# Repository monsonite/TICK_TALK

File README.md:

# TICK_TALK
## An experimental 8-bit, bit serial computer.

## Hebden Bridge Workshop Update  25-08-24

OSHCamp 2024

TICK Workshop Update.

Thanks to the 16 people who attended the 1st TICK workshop session at Hebden Bridge, on Sunday August 25th.

Most kits were assembled without too many problems, and several were close to completion at the end of the afternoon.

Unfortunately some components were misplaced and not found until late in the afternoon, close to packing up time, but workarounds were employed.

Attendees should make contact me via email at k*n.boat@gmail.com - replacing the "t" with the 1st letter of my 1st name.

### Points Arising.

1.  The 74HC4060.dig file is now available. Download it and place it in the Lib  (libraries) folder of where you have installed "Digital"  - ideally under 

\Digital\Digital\lib\DIL Chips\74xx\counter

Then restart Digital and select components, custom, update and it should then be available.

2. Tick now has a Hackaday.io project page here:

https://hackaday.io/project/197333-tick-a-novel-homebrew-mcu-architecture-in-28-ics

Please feel free to join the project team and message me in the team messaging section.

3. It would be sensible to convert the Eagle CAD pcb schematic and pcb layout files to KiCad - to allow greater accessibility to interested users. I will investigate importing the schematic into Kicad, with the aim of generating the next iteration of the pcb using Kicad.

4. As the workshop was primarily focussed on assembly of the pcb in the time available, the Pi Pico firmware aspects of the project remained virtually unmentioned.

The principal role of the Pico is to emulate a 64K x16-bit ROM. It does this by "sniffing" the ROM address lines generated from the Program Counter, and using the two 74HC595 shift registers (U26, U27) located under the Pi Pico, to output the 16-bit value from that ROM address onto the Instruction Bus.

5. The 6-way JST cables supplied will allow the Pi Pico access to both the ROMulator Port X2 (on the left) and the SPI Port X1 (on the right). Details of these connectors and the modifications to the wiring of the cable to the Pico GPIO pins 18 to 21 and 26 to 29 will be released shortly in a separate document'

6.  I have received notification from PCBWay in China and they are prepared to sponsor the manufacture of the next version of the Tick PCB.

I am tempted to have a SMT version assembled in China - so it will be smaller, lighter and have better features.

I would like your feedback over, whether you would like to receive this SMT version in the Autumn.

Please send feedback to my Gmail address.

Ken

Update  - Lissa has created a new discord server for TICK

try this invite code.

https://discord.gg/FmW9dqFGb5

/*************************************************************************************************************************

TICK is an experimental 8-bit, serial arithmetic CPU designed around the commonly available 74HCxx logic series.

TICK uses 26 74HXxx ICs, plus a 32K byte RAM and a 64K x 16-bit ROM - or a ROM emulator.

TICK fits onto a 4-layer PCB, sized just 110mm x 110mm. It has 5 principal connectors that allow you to access all of the main signals and buses. Low cost 6-way JST XH ribbon cables are used to hook up the TICK serial interface bus and the Pi Pico SPI.  A 40 way 2.54mm pitch header allows access to the parallel buses.

USB (power) is supplied either through a USB microB connector or via USB C connector of the the Clone Pi Pico "ROMulator".

PCB Headers are included that will allow a very low-cost Raspberry Pi Pico (clone) to be plugged in, providing emulation of the ROM and also implementing a simple serial interface to a laptop or PC.

TICK has evolved slowly over several months, and this repo reflects the most recent design files, manufacturing data and BOM. The earlier repo "TICK" is purely reserved for earlier work. All current and future developments will be documented here.

TICK started life a few months ago and is highly influenced by the the developments I did on "MITE" its 16-bit Cousin. Here the basics of the timing pulse generator and ALU were thashed out to the point that I am happy to utilise them in a new design.

Much of the combinational logic has been rationalised, and short of implementing the ALU and control logic in a ROM, I believe that I have reached a point where the logic is stable, and not reduced to a blackbox ROM.

TICK is 26 74HCxx ICs plus a ROM and RAM.

The ICs are utilised in 5 main sub-circuits:

1. Clock Sequencer and Timing Pulse Generator.

2. Instruction Decoder

3. ALU and PC Incrementer, plus Jump logic.

4. Memory Control Hardware.

5. GPIO and ROMulator interfaces.

In an ideal world,  TICK would be a BlackBox with just 2 wires for power, and 2 wires for data in and data out. If you look at a landline telephone or broadband modem, they only have 2 wires or 4 wires. However for the purposes of this project we reqire syncronous data transfer - and that needs a clock that is shared between all nodes.

In general terms, TICK communicates with external devices via an SPI compatible interface.

## Architecture

TICK is highly influenced by Marcel van Kervinck's 8-bit Gigatron TTL Computer. The Gigatron used ten ICs in its ALU, I can do it serially in two. However a bit-serial design needs additional ICs to implement the clock sequencer, the timing pulse generator and the SRAM and Jump logic.

It is very marginal whether an 8-bit serial architecture will have fewer ICs than an 8-bit parallel design. Bit Serial really comes into fruition when you have a wordsize of 16 or more bits.

So the motivation for developing TICK was to make an intelligent node that can interface to SPI serial peripherals and other intelligent nodes. It won't be the fastest computer on the planet - but it should be able to compete with 1970s/80s 8-bit workhorses, like the 6502, Z80, 8051, 6309 etcand even older machines that predate the microprocessor - such as the  PDP-8 (1965) and the EDUC8 (1974).

TICK is a modified Harvard architecture.  Address and data from the ROM are conveyed on separate buses to those of the RAM. Simple shift registers are used to convert between the serial and parallel domains. A task that they can do very efficiently.

### Registers

TICK has a single 8-bit accumulator AC. AC may be loaded with an 8-bit literal direct from the lower 8 ROM data lines, or AC can be loaded with data addressed from the 32K x 8-bit SRAM.

As well as the Accumulator AC, TICK has a 16-bit wide general purpose register known as the B-Register. The B-Reg is 16-bits wide, in order to accept a 16-bit word, in parallel from the ROM and either use that as a indirect RAM address, or load it into the ROM Program Counter (PC) to perform a Conditional Branch or a 16-bit Long Jump.

The PC mentioned above is also 16-bits wide and can cover the full 16 bits of the ROM addressing range. A 16-bit jump is non-conditional, but an 8-bit "page" branch is conditional on the ZERO and SIGN flags from the Accumulator.

## Circuit Description (Draft 20-08-24)

Tick is an experimental, 8-bit, bit serial computer designed to interface to SPI peripherals and memory.

It has a 16-bit Program Counter, a 16-bit B-Register, an 8-bit Accumulator and an 8-bit Input Register.

The circuit may be subdivided into several sub-sections for easier analysis.

1. Clock Sequencer and Timing Pulse Generator (TPG)
2. Instruction Decoder
3. Program Counter (PC)
4. Arithmetic and Logic Unit (ALU)
5. Conditional Branch Logic
6. Memory Access
7. Input/Output  (I/O)
8. ROM Emulation

## 1. Clock Sequencer and Timing Pulse Generator (TPG)

This is at the heart of the design and co-ordinates all of the control signals.

A 14-bit binary counter U6 (74HC4060) provides a crystal oscillator with a 16MHz crystal Q1. This is divided down to provide 10, link selectable clock outputs from 1Khz (approx) to 1MHz. The selected clock feeds a 4-bit counter, U8 (74HC161) and this is used to generate a burst of 16 clock pulses for the Program Counter (PC-CLK) and 8 gated clock pulses (GCLK) for the 8-bit shift registers. A SR latch formed around NAND U7 (74HC00) with triple input AND U11 (74HC11) provides a means of gating the clock to generate PC-CLK and GCLK.

The terminal count of the 74HC161 (RCO) is used to feed a chain of 4, D-type flipflops U9 (74HC175), and these "top and tail" pulses T0, T1, T17 T18 and their complements are used to synchronise the loading of shift registers andread/write access to the SRAM.

A power-on reset circuit is formed around U19A and U19B. This resets all shift registers and counters when power is applied to the circuit. There is also a RESET switch S13, which allows a manual reset to be performed.

## 2. Instruction Decoder

The instruction from the ROM is 16-bits wide and consists od an instruction field IR7:0 and a data field P7:P0.

The instruction field is further divided into a 4-bit operand  IR7:IR4, and a condition field IR3:IR0.

If IR7=0, the remainder of the 16-bit word is treated as a literal and is loaded into the B-Register.

If IR7=1, this indicates a RAM memory reference instruction with IR6:4 defining the operation, and the remainder of the instruction word IR3:0 and P7:0 treated as a 12-bit address which is output onto the RAM address bus MA11:MA0.

Instruction decoding is done with 4 or 5 "basic gate" ICs. As entirely combinational logic, it could also be implemented in a small ROM, or even with a diode matrix.

Instruction decoding begins with U10 (74HC138) a 3 to 8 line decoder, which performs the primary stage of decoding. 

Here the instruction field IR6:4 is decoded into the 8 instruction groups, with one of its "Y" outputs being set low for each individual instruction group - as follows.

/Y0		LOAD
/Y1		AND
/Y2		XOR
/Y3		OR
/Y4		ADD
/Y5		SUB
/Y6		STORE
/Y7		JUMP

These low going outputs are further combined in logic U11, (74HC11), U12 (74HC86) and U13 (74HC00) to provide a series of control signals, time selected by the timing pulses T0, T1, T17 and T18.

Quad 2-input NAND gate U13 does the bulk of the secondary decoding, where instruction groups /Y0 to /Y7 are gated with timeslot pulses. 

The two XOR gates U12B and U12C have one input tied high and thus act as simple inverters. U12A is also an inverter and is connectedas an 8-input wired OR gate with 8 input diodes and a pull-down resistor, used to detect when the output of the Accumulator or memory on the data bus is equal to zero.

U11 is a triple 3-input AND. U11A detects if any of the Boolean instructions have been selected (/Y1, /Y2, /Y3) and is used to suppress the carry.

## 3. Program Counter.

This is a 16-bit counter and consists of two 74HC595 serial in parallel out (SIPO) shift registers U2 and U3 connected in series. As a bit serial computer, it is reasonable to use shift registers and a half adder to create a Program Counter, especially as it can be loaded from a serial data stream.

The registers convert a serial bitstream into a parallel address, which is used to address the 64K x 16-bit ROM (U1 AT27C1024). For development purposes, the ROM is replaced with a Pi Pico clone, for a more efficient development cycle.

The 74HC595 is a SIPO shift register, with all outputs connected to an octal tristate latch. Once the shift register contains the required address, this can then be latched onto the output pins, where it will remain for the whole duration of the machine cycle. In this respect, the PC "freezes" the address and as such acts as the Instruction Register, holding the Instruction for the complete Fetch, Execute, Writeback cycle. As the lower 12-bits of the ROM contain the effective memory address (EA), the address of the operand read, will be retained for the writeback operation.

A Program Counter has two modes of operation, either to increment the ROM address by 1 at the end of each machine cycle, or to load the shift registers from an external serial source to allow a jump to be executed. 

The PC increment hardware is based around a half adder, followed by a 2-input multiplexer. The mux chooses between the increment mode and the load (jump) mode.

The PC half adder is provided by one half of a 4-bit full adder (74HC283 U14). The multiplexer is one half of a 74HC126, quad tristate buffer (U15). The other halves of U14 and U15 are used in the ALU, so not wasted. Instruction group 7 "Jump" is used to swich the PC multiplexer between its +1 increment mode and the jump mode, where it is loaded with data from the B-Register, which has been loaded from the ROM or from and external source.

## 4. Arithmetic and Logic Unit (ALU)

The ALU is based around a full adder, in this case provided by U14 (74HC283) four bit adder that has been partitioned to provide a half adder for the Program Counter and a full adder for the ALU. The full adder can perform subtraction too, by inverting the input from the B-register and adding 1, by way of the Carry input.

The full adder provides sum (XOR) and carry (AND) outputs, which are selected using a 2-input multiplexer, provided by U15 (74HC126). This allows the ZERO, AND, XOR and OR bitwise Boolean logic functions to be selected by way of two instruction control lines I0 and I1. If a Boolean function is selected, the carry propagation from bit to bit is suppressed.

## 5. Conditional Branch Logic

During a conditional branch, the 4-bit instruction field IR3:0 defines the condition as follows by testing the ZERO flag and the MSB of the Accumulator:

0000		Long Jump
0001		AC > 0  	BGT
0010		AC < 0		BLT
0011		AC != 0		BNE
0100		AC = 0		BEQ
0101		AC >= 0		BGE
0110		AC <= 0		BLE
0111		Branch Always
1xxx		
  
A 4 input multiplexer, U23 (74HC153) receives the condition field IR2:0 on inputs C2:C0. The JUMP signal is used to enable the multiplexer via pin 1.

The ALU status bits ZERO and SIGN (BUS7), are applied to select inputs A and B. If a condition is met the BCC output on pin 7 is raised.

The other half of the multiplexer is not used.

The BCC output is combined in NAND U28 (74HC00) to provide a LONGJUMP control signal if IR3 = 0. If IR3 = 0 the jump address is taken from the 11 lower bits of the instruction word, limiting it to 0 to 2047 in RAM.

## 6. Memory Access.

The 32K byte RAM U18 (62256) is read onto the data bus during timeslot T0, and written back to during timeslot T18.

The address for the RAM comes from the full 16-bit output of the Instruction ROM but with the exception that IR7=1, so a range of 32768 addresses may be reached.

There are 2 distinct forms of Load instruction:

IR7=1 Memory Reference Instruction 

IR3:IR2 and P7:0 forms a 12-bit address for the A operand to place in the Accumulator. This applies to LOAD, AND, XOR, AND, ADD, SUB and STORE instructions.

IR7=0.

Load Accumulator with data from address IR7:0 and P7:0 thus covering addresses 0 to 32767, which is the full extent of the fitted RAM.

Load the B-Register with the 15 bit constant, IR6:0 and P7:0

## 7. Input/Output  (I/O)

TICK is intended to work with SPI peripherals and memory. As such it implements a basic SPI bus with MOSI, MISO, SCLK and /SS signals.

The serial output of the Accumulator U17 (74HC299) is fed through a tristate buffer U24A and sends this MOSI signal to connector X1 pin 2. The MISO signal is received by U22 (74HC595) 8-bit tristate, latchable shift register on X1 pin 3 and can be gated onto the 8-bit data bus. The serial clock X1 pin 4 is just the 8 cycle gated clock burst, GCLK. The slave select /SS or /CE (chip enable) is the inverted output Q4 of the gating counter U8 (74HC161). A maximum SCLK of 1MHz can be achieved from the current 16MHz clock crystal oscillator.

## 8. ROM Emulator and SPI Peripherals.

Whilst TICK was designed to have firmware coded into a 64K x 16-bit ROM, U1 (AT27C1024) it makes sense to emulate the ROM with a small microcontroller - in this case a low cost clone of the popular Raspberry Pi Pico module.

The Pico plugs into 2 x 20 way female pcb socket J3 on the left hand edge of the pcb.  It's GPIO lines 0 to 15, "sniff" the ROM address generated by the Program Counter, and then look up the associated instruction word from a table of ROM contents held in the flash memory of the Pico. This 16-bit word is then output to a pair of 74HC595 shift registers, U26 and U27 located below the Pico module, which present the "ROM" data to the relevant ROM data lines IR7:0 and P7:0.

The Pi Pico provides regulated 3V3 supply for the TICK board and also a USB serial port for debugging. Unused GPIO, ADC chanels and other resources on the Pico can be used to support the TICK board. The Pico can act as a smart serial peripheral and connect to the TICK via the SPI port connector X1.

Xpansion Ports, X1, X2 - Connector Pin-Outs

### X2  (left to right) ROMulator Port

Used to emulate a 64K x 16-bit ROM and provide serial port access to laptop.

1   3V3          Connects to VCC to power the Tick PCB

2   /PC_EN       Set low to eneable the Program counter

3   SER_IN       Serial data from Pi Pico to shift registers U26 and U27

4   SER_CLK      Clock from Pi Pico to synchronise the serial data packets and clock U26 and U27

5   STB          A strobe pulse at the end of the data packet that latches the data onto the Instruction Bus

6   0V           Connects to GND plane (0V) of Tick pcb

### X1  (left to right) SPI Port

Used to connect the Tick CPU to SPI peripherals or use the Pi Pico as a smart peripheral.

1   3V3          Connects to VCC to power the Tick PCB

2   MOSI         8-bit Serial data output from Tick Accumulator to PI Pico MISO

3   MISO         8-bit Serial data output from PI Pico MOSI to Tick input register U22 (74HC595).

4   GCLK         Gated clock burst generated by Tick to synchronise serial data transfer

5   /SS          Slave Select - signal goes low for the duration of the GCLK burst. Used to latch data into the SPI slave device

6   0V           Connects to GND plane (0V) of Tick pcb

Two 6-way JST cables are used to connect X1 and X2 to the GPIO and 3V3 supply from the Pi Pico. These need to have a couple of wires swapped  to form the following connections:

### X2 - ROMulator Port 

1       Pico 3V3

2       Pico 29  /PC_EN

3       Pico 28  Serial Data

4       Pico 27  Serial Clock

5       Pico 26  Latch data

6       Pico GND

### X1 - SPI Port 

1       Pico 3V3

2       Pico 19  Pico SPI 0 MISO

3       Pico 16  Pico SPI 0 MOSI

4       Pico 18  GCLK

5       Pico 17  /SS 

6       Pico GND

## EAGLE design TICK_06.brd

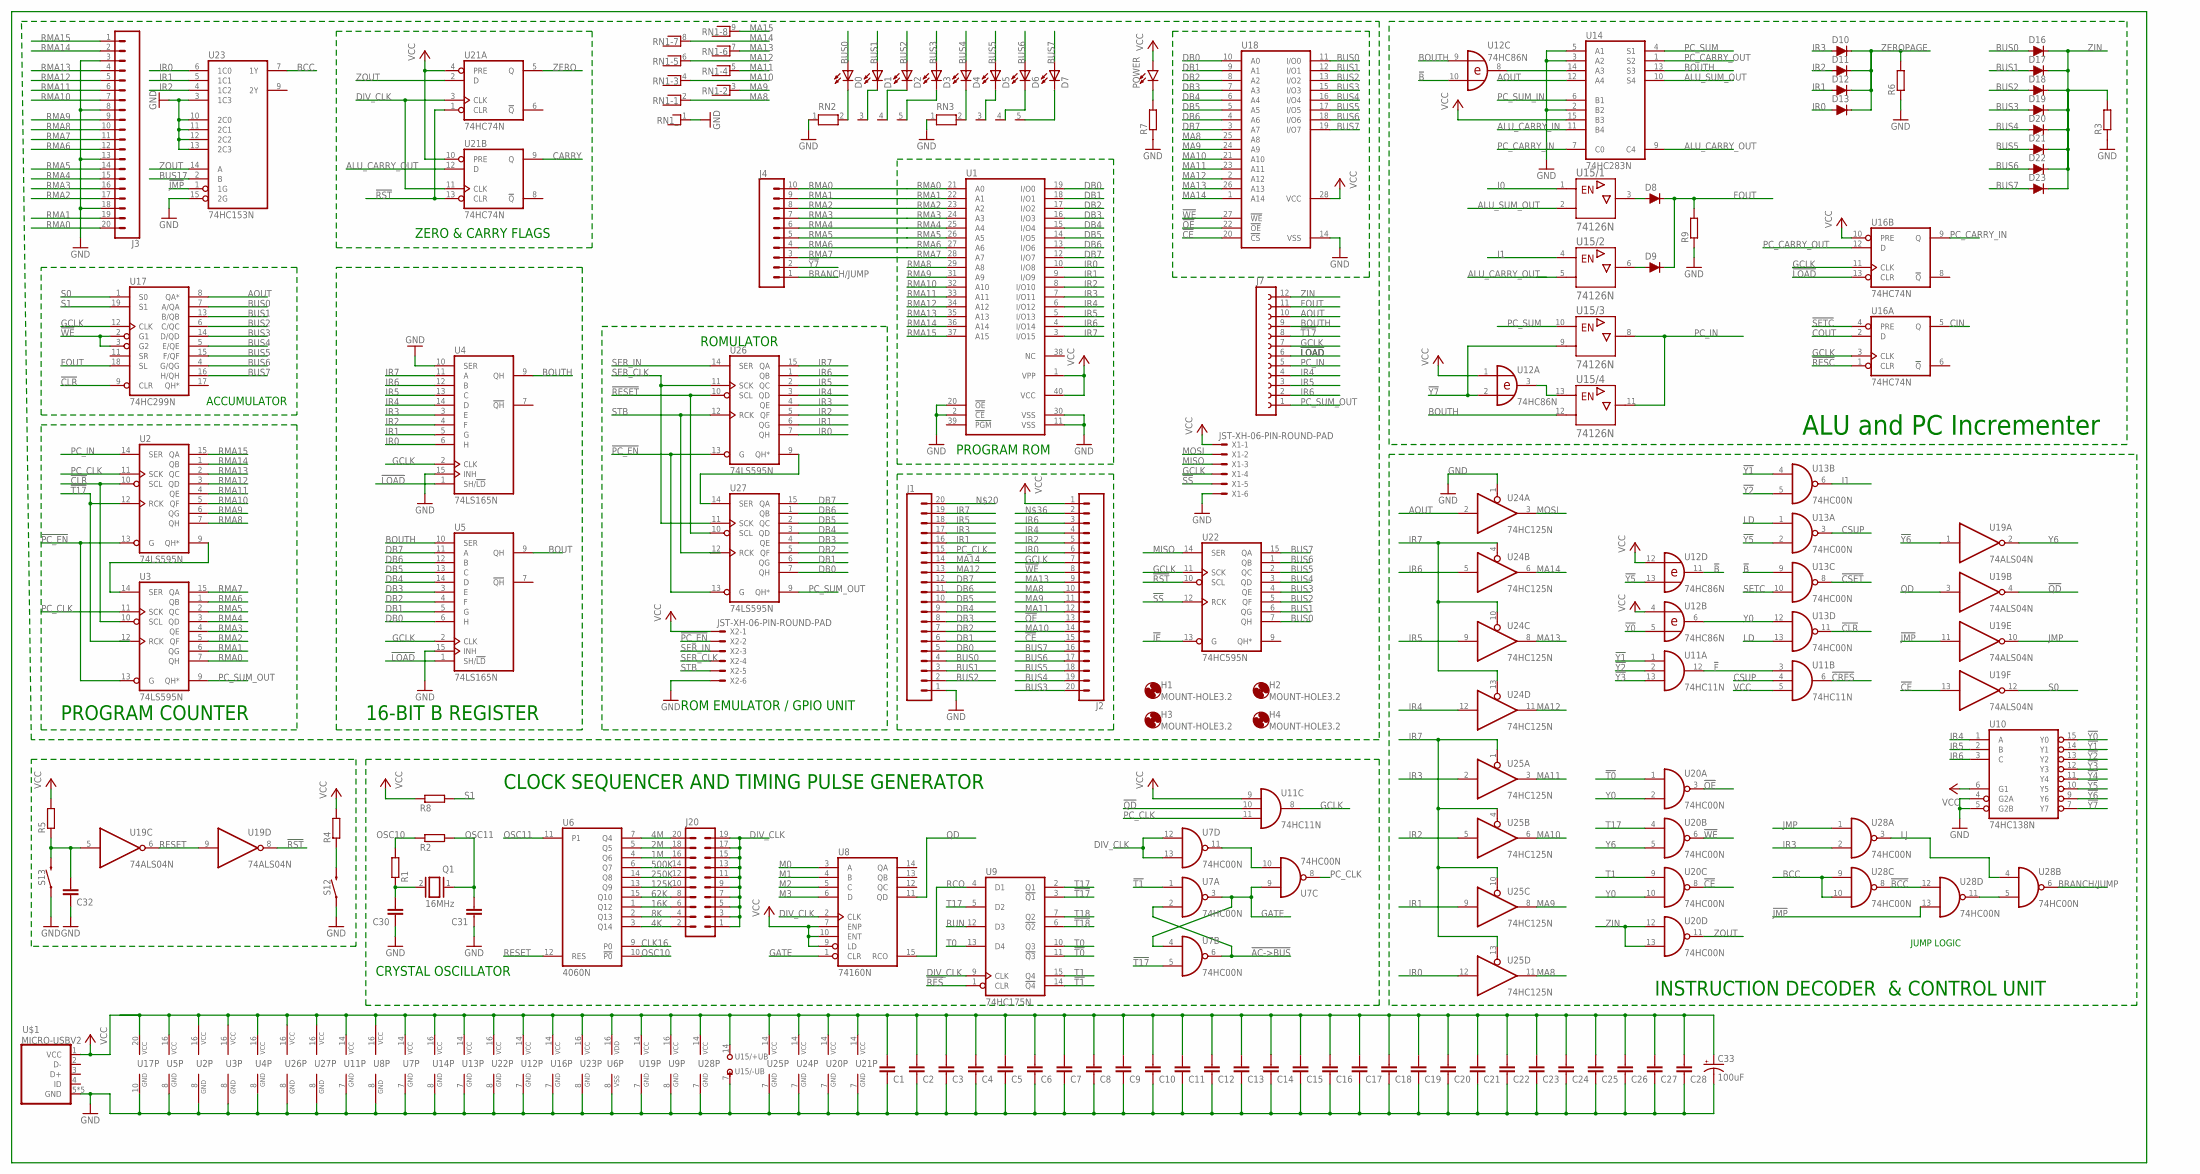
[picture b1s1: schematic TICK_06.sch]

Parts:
C1, C2, C3, C4, C5, C6, C7, C8, C9, C10, C11, C12, C13, C14, C15, C16, C17, C18, C19, C20, C21, C22, C23, C24, C25, C26, C27, C28, C30, C31, C32: C-EU025-024X044; C025-024X044
C33: 100uF; CPOL-RADIAL-2.5MM-6.5MM
D0, D1, D2, D3, D4, D5, D6, D7: LED3MM
D8, D9, D10, D11, D12, D13, D17, D18, D19, D20, D21, D22, D23: 200mA/100V/1V; DIODE-1N4148
D16: 200mA/100V/1V; DIODE-1N4148-KIT
H1, H2, H3, H4: MOUNT-HOLE3.2; 3,2
J1, J2, J3: CONN_20NO_SILK_KIT; 1X20_NO_SILK_KIT
J4: CONN_10"; 1X10
J7: FE12-1; FE12
J20: MA10-2
POWER: LED3MM; LED_3MM
Q1: 16MHz; QS
R1, R2, R3, R4, R5, R6, R7, R8, R9: R-EU_0204/5; 0204/5
RN1: RNX8; RN-9
RN2, RN3: RN04; RN-5
S12, S13: MOMENTARY-SWITCH-SPST-PTH-6.0MM; TACTILE_SWITCH_PTH_6.0MM
U1: 27C1024HG; DIL40
U2, U3, U26, U27: 74LS595N; DIL16
U4, U5: 74LS165N; DIL16
U6: 4060N; DIL16
U7, U13, U20, U28: 74HC00N; DIL14
U8: 74160N; DIL16
U9: 74HC175N; DIL16
U10: 74HC138N; DIL16
U11: 74HC11N; DIL14
U12: 74HC86N; DIL14
U14: 74HC283N; DIL16
U15: 74126N; DIL14
U16, U21: 74HC74N; DIL14
U17: 74HC299N; DIL20
U18: 62256P; DIL28-6
U19: 74ALS04N; DIL14
U22: 74HC595N; DIL16
U23: 74HC153N; DIL16
U24, U25: 74HC125N; DIL14
U$1: MICRO-USBV2; MICRO-USB-2
X1, X2: JST-XH-06-PIN-ROUND-PAD; JST-XH-06-PACKAGE-ROUND-PAD

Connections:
1M: J20.16, U6.4 (Q6)
2M: J20.18, U6.5 (Q5)
4K: J20.2, U6.3 (Q14)
4M: J20.20, U6.7 (Q4)
8K: J20.4, U6.2 (Q13)
16K: J20.6, U6.1 (Q12)
62K: J20.8, U6.15 (Q10)
125K: J20.10, U6.13 (Q9)
250K: J20.12, U6.14 (Q8)
500K: J20.14, U6.6 (Q7)
!AC->BUS: U7.2 (I1), U7.6 (O)
!B: U12.10 (I1), U12.11 (O), U13.9 (I0)
!BCC: U28.8 (O), U28.12 (I0)
!CE: J2.15, U18.20 (!CS), U19.13 (I), U20.8 (O)
!CLR: U2.10 (SCL), U3.10 (SCL), U13.11 (O), U17.9 (CLR)
!CRES: U11.6 (O)
!CSET: U13.8 (O)
!F: U11.3 (I0), U11.12 (O)
!IE: U22.13 (G)
!JMP: U19.11 (I), U23.1 (1G), U28.13 (I1)
!LOAD: J7.6, U4.1 (SH/!LD), U5.1 (SH/!LD), U16.13 (CLR)
!OE: J2.13, U18.22 (!OE), U20.3 (O)
!PC_EN: U2.13 (G), U3.13 (G), U26.13 (G), U27.13 (G), X2.2
!QD: U11.10 (I1), U19.4 (O)
!RES: U9.1 (CLR)
!RESC: U16.1 (CLR)
!RESET: U26.10 (SCL), U27.10 (SCL)
!RST: U19.8 (O), U21.1 (CLR), U21.13 (CLR), U22.10 (SCL)
!SETC: U16.4 (PRE)
!SS: U22.12 (RCK), X1.5
!T0: U9.11 (!Q3), U20.1 (I0)
!T1: U7.1 (I0), U9.14 (!Q4)
!T17: J7.8, U2.12 (RCK), U3.12 (RCK), U7.5 (I1), U9.3 (!Q1)
!T18: U9.6 (!Q2)
!WE: J2.8, U17.2 (G1), U17.3 (G2), U18.27 (!WE), U20.6 (O)
!Y0: U10.15 (Y0), U12.5 (I1)
!Y1: U10.14 (Y1), U11.1 (I0), U13.4 (I0)
!Y2: U10.13 (Y2), U11.2 (I1), U13.5 (I1)
!Y3: U10.12 (Y3), U11.13 (I2)
!Y4: U10.11 (Y4)
!Y5: U10.10 (Y5), U12.13 (I1), U13.2 (I1)
!Y6: U10.9 (Y6), U19.1 (I)
!Y7: J4.2, U10.7 (Y7), U12.2 (I1), U15.9 (A)
ALU_CARRY_IN: U14.11 (B4)
ALU_CARRY_OUT: U14.9 (C4), U15.5 (A), U21.12 (D)
ALU_SUM_OUT: U14.10 (S4), U15.2 (A)
AOUT: J7.10, U14.12 (A4), U17.8 (QA*), U24.2 (I)
BCC: U23.7 (1Y), U28.9 (I0), U28.10 (I1)
BOUT: U5.9 (QH)
BOUTH: J7.9, U4.9 (QH), U5.10 (SER), U12.9 (I0), U14.13 (S3), U15.12 (A)
BRANCH/JUMP: J4.1, U28.6 (O)
BUS0: D0.A, D16.A, J1.4, U17.7 (A/QA), U18.11 (I/O0), U22.7 (QH)
BUS1: D1.A, D17.A, J1.3, U17.13 (B/QB), U18.12 (I/O1), U22.6 (QG)
BUS2: D2.A, D18.A, J1.2, U17.6 (C/QC), U18.13 (I/O2), U22.5 (QF)
BUS3: D3.A, D19.A, J2.20, U17.14 (D/QD), U18.15 (I/O3), U22.4 (QE)
BUS4: D4.A, D20.A, J2.19, U17.5 (E/QE), U18.16 (I/O4), U22.3 (QD)
BUS5: D5.A, D21.A, J2.18, U17.15 (F/QF), U18.17 (I/O5), U22.2 (QC)
BUS6: D6.A, D22.A, J2.17, U17.4 (G/QG), U18.18 (I/O6), U22.1 (QB)
BUS7: D7.A, D23.A, J2.16, U17.16 (H/QH), U18.19 (I/O7), U22.15 (QA)
BUS17: U23.2 (B)
CARRY: U21.9 (Q)
CIN: U16.5 (Q)
CLK16: U6.9 (P0)
COUT: U16.2 (D)
CSUP: U11.4 (I1), U13.3 (O)
DB0: J1.5, U1.19 (I/O0), U5.6 (H), U18.10 (A0), U27.7 (QH)
DB1: J1.6, U1.18 (I/O1), U5.5 (G), U18.9 (A1), U27.6 (QG)
DB2: J1.7, U1.17 (I/O2), U5.4 (F), U18.8 (A2), U27.5 (QF)
DB3: J1.8, U1.16 (I/O3), U5.3 (E), U18.7 (A3), U27.4 (QE)
DB4: J1.9, U1.15 (I/O4), U5.14 (D), U18.6 (A4), U27.3 (QD)
DB5: J1.10, U1.14 (I/O5), U5.13 (C), U18.5 (A5), U27.2 (QC)
DB6: J1.11, U1.13 (I/O6), U5.12 (B), U18.4 (A6), U27.1 (QB)
DB7: J1.12, U1.12 (I/O7), U5.11 (A), U18.3 (A7), U27.15 (QA)
DIV_CLK: J20.1, J20.3, J20.5, J20.7, J20.9, J20.11, J20.13, J20.15, J20.17, J20.19, U7.12 (I0), U7.13 (I1), U8.2 (CLK), U9.9 (CLK), U21.3 (CLK), U21.11 (CLK)
FOUT: D8.C, D9.C, J7.11, R9.2, U17.18 (SL)
GATE: U7.3 (O), U7.4 (I0), U7.9 (I0), U8.1 (CLR)
GCLK: J2.7, J7.7, U4.2 (CLK), U5.2 (CLK), U11.8 (O), U16.3 (CLK), U16.11 (CLK), U17.12 (CLK), U22.11 (SCK), X1.4
GND: C1.1, C2.1, C3.1, C4.1, C5.1, C6.1, C7.1, C8.1, C9.1, C10.1, C11.1, C12.1, C13.1, C14.1, C15.1, C16.1, C17.1, C18.1, C19.1, C20.1, C21.1, C22.1, C23.1, C24.1, C25.1, C26.1, C27.1, C28.1, C30.1, C31.1, C32.1, C33.2 (-), J1.1, J3.3, J3.8, J3.13, J3.18, R3.1, R6.1, R7.1, R9.1, RN1.1, RN2.1, RN3.1, S12.1, S13.1, U1.2 (!CE), U1.11 (VSS), U1.20 (!OE), U1.30 (VSS), U2.8 (GND), U3.8 (GND), U4.8 (GND), U4.10 (SER), U4.15 (INH), U5.8 (GND), U5.15 (INH), U6.8 (VSS), U7.7 (GND), U8.8 (GND), U9.8 (GND), U10.4 (G2A), U10.5 (G2B), U10.8 (GND), U11.7 (GND), U12.7 (GND), U13.7 (GND), U14.2 (B2), U14.3 (A2), U14.5 (A1), U14.8 (GND), U15.7 (-UB), U16.7 (GND), U17.10 (GND), U18.14 (VSS), U19.7 (GND), U20.7 (GND), U21.7 (GND), U22.8 (GND), U23.3 (1C3), U23.8 (GND), U23.10 (2C0), U23.11 (2C1), U23.12 (2C2), U23.13 (2C3), U23.15 (2G), U24.1 (OE), U24.7 (GND), U25.7 (GND), U26.8 (GND), U27.8 (GND), U28.7 (GND), U$1.5 (GND), U$1.P$1 (GND), U$1.P$2 (GND), U$1.P$3 (GND), U$1.P$4 (GND), X1.6, X2.6
I0: U15.1 (G)
I1: U13.6 (O), U15.4 (G)
IR0: D13.A, J2.6, U1.10 (I/O8), U4.6 (H), U23.6 (1C0), U25.12 (I), U26.7 (QH)
IR1: D12.A, J1.16, U1.9 (I/O9), U4.5 (G), U23.5 (1C1), U25.9 (I), U26.6 (QG)
IR2: D11.A, J2.5, U1.8 (I/O10), U4.4 (F), U23.4 (1C2), U25.5 (I), U26.5 (QF)
IR3: D10.A, J1.17, U1.7 (I/O11), U4.3 (E), U25.2 (I), U26.4 (QE), U28.2 (I1)
IR4: J2.4, J7.4, U1.6 (I/O12), U4.14 (D), U10.1 (A), U24.12 (I), U26.3 (QD)
IR5: J1.18, J7.3, U1.5 (I/O13), U4.13 (C), U10.2 (B), U24.9 (I), U26.2 (QC)
IR6: J2.3, J7.2, U1.4 (I/O14), U4.12 (B), U10.3 (C), U24.5 (I), U26.1 (QB)
IR7: J1.19, U1.3 (I/O15), U4.11 (A), U24.4 (OE), U24.10 (OE), U24.13 (OE), U25.1 (OE), U25.4 (OE), U25.10 (OE), U25.13 (OE), U26.15 (QA)
JMP: U19.10 (O), U28.1 (I0)
LD: U13.1 (I0), U13.13 (I1)
LJ: U28.3 (O), U28.4 (I0)
M0: U8.3 (A)
M1: U8.4 (B)
M2: U8.5 (C)
M3: U8.6 (D)
MA8: J2.10, RN1.2, U18.25 (A8), U25.11 (O)
MA9: J2.11, RN1.3, U18.24 (A9), U25.8 (O)
MA10: J2.14, RN1.4, U18.21 (A10), U25.6 (O)
MA11: J2.12, RN1.5, U18.23 (A11), U25.3 (O)
MA12: J1.13, RN1.6, U18.2 (A12), U24.11 (O)
MA13: J2.9, RN1.7, U18.26 (A13), U24.8 (O)
MA14: J1.14, RN1.8, U18.1 (A14), U24.6 (O)
MA15: RN1.9
MISO: U22.14 (SER), X1.3
MOSI: U24.3 (O), X1.2
unnamed: D0.K (C), RN2.2
unnamed: D1.K (C), RN2.3
unnamed: U28.5 (I1), U28.11 (O)
unnamed: U7.10 (I1), U7.11 (O)
unnamed: D2.K (C), RN2.4
unnamed: D8.A, U15.3 (Y)
unnamed: R4.1, S12.3 (2)
unnamed: C32.2, R5.1, S13.3 (2), U19.5 (I)
unnamed: POWER.K (C), R7.2
unnamed: U12.8 (O), U14.14 (A3)
unnamed: D9.A, U15.6 (Y)
unnamed: D3.K (C), RN2.5
unnamed: D4.K (C), RN3.2
unnamed: D5.K (C), RN3.3
unnamed: D6.K (C), RN3.4
unnamed: D7.K (C), RN3.5
unnamed: U2.9 (QH*), U3.14 (SER)
unnamed: U26.9 (QH*), U27.14 (SER)
unnamed: U12.3 (O), U15.13 (G)
unnamed: C30.2, Q1.2, R1.1
OSC10: R1.2, R2.1, U6.10 (!P0)
OSC11: C31.2, Q1.1, R2.2, U6.11 (P1)
PC_CARRY_IN: U14.7 (C0), U16.9 (Q)
PC_CARRY_OUT: U14.1 (S2), U16.12 (D)
PC_CLK: J1.15, U2.11 (SCK), U3.11 (SCK), U7.8 (O), U11.11 (I2)
PC_IN: J7.5, U2.14 (SER), U15.8 (Y), U15.11 (Y)
PC_SUM: U14.4 (S1), U15.10 (G)
PC_SUM_IN: U14.6 (B1)
PC_SUM_OUT: J7.1, U3.9 (QH*), U27.9 (QH*)
QD: U8.11 (QD), U19.3 (I)
RCO: U8.15 (RCO), U9.4 (D1)
RESET: U6.12 (RES), U19.6 (O), U19.9 (I)
RMA0: J3.20, J4.10, U1.21 (A0), U3.7 (QH)
RMA1: J3.19, J4.9, U1.22 (A1), U3.6 (QG)
RMA2: J3.17, J4.8, U1.23 (A2), U3.5 (QF)
RMA3: J3.16, J4.7, U1.24 (A3), U3.4 (QE)
RMA4: J3.15, J4.6, U1.25 (A4), U3.3 (QD)
RMA5: J3.14, J4.5, U1.26 (A5), U3.2 (QC)
RMA6: J3.12, J4.4, U1.27 (A6), U3.1 (QB)
RMA7: J3.11, J4.3, U1.28 (A7), U3.15 (QA)
RMA8: J3.10, U1.29 (A8), U2.7 (QH)
RMA9: J3.9, U1.31 (A9), U2.6 (QG)
RMA10: J3.7, U1.32 (A10), U2.5 (QF)
RMA11: J3.6, U1.33 (A11), U2.4 (QE)
RMA12: J3.5, U1.34 (A12), U2.3 (QD)
RMA13: J3.4, U1.35 (A13), U2.2 (QC)
RMA14: J3.2, U1.36 (A14), U2.1 (QB)
RMA15: J3.1, U1.37 (A15), U2.15 (QA)
RUN: U9.12 (D3)
S0: U17.1 (S0), U19.12 (O)
S1: R8.2, U17.19 (S1)
SER_CLK: U26.11 (SCK), U27.11 (SCK), X2.4
SER_IN: U26.14 (SER), X2.3
SETC: U13.10 (I1)
STB: U26.12 (RCK), U27.12 (RCK), X2.5
T0: U9.10 (Q3), U9.13 (D4)
T1: U9.15 (Q4), U20.9 (I0)
T17: U9.2 (Q1), U9.5 (D2), U20.4 (I0)
T18: U9.7 (Q2)
VCC: C1.2, C2.2, C3.2, C4.2, C5.2, C6.2, C7.2, C8.2, C9.2, C10.2, C11.2, C12.2, C13.2, C14.2, C15.2, C16.2, C17.2, C18.2, C19.2, C20.2, C21.2, C22.2, C23.2, C24.2, C25.2, C26.2, C27.2, C28.2, C33.1 (+), J2.1, POWER.A, R4.2, R5.2, R8.1, U1.1 (VPP), U1.40 (VCC), U2.16 (VCC), U3.16 (VCC), U4.16 (VCC), U5.16 (VCC), U6.16 (VDD), U7.14 (VCC), U8.7 (ENP), U8.9 (LD), U8.10 (ENT), U8.16 (VCC), U9.16 (VCC), U10.6 (G1), U10.16 (VCC), U11.5 (I2), U11.9 (I0), U11.14 (VCC), U12.1 (I0), U12.4 (I0), U12.12 (I0), U12.14 (VCC), U13.14 (VCC), U14.15 (B3), U14.16 (VCC), U15.14 (+UB), U16.10 (PRE), U16.14 (VCC), U17.20 (VCC), U18.28 (VCC), U19.14 (VCC), U20.14 (VCC), U21.4 (PRE), U21.10 (PRE), U21.14 (VCC), U22.16 (VCC), U23.16 (VCC), U24.14 (VCC), U25.14 (VCC), U26.16 (VCC), U27.16 (VCC), U28.14 (VCC), U$1.1 (VCC), X1.1, X2.1
Y0: U13.12 (I0), U20.2 (I1), U20.10 (I1)
Y6: U19.2 (O), U20.5 (I1)
ZERO: U21.5 (Q)
ZEROPAGE: D10.C, D11.C, D12.C, D13.C, R6.2
ZIN: D16.C, D17.C, D18.C, D19.C, D20.C, D21.C, D22.C, D23.C, J7.12, R3.2, U20.12 (I0), U20.13 (I1)
ZOUT: U20.11 (O), U21.2 (D), U23.14 (A)

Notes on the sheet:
ALU and PC Incrementer
CLOCK SEQUENCER AND TIMING PULSE GENERATOR
CRYSTAL OSCILLATOR
ZERO & CARRY FLAGS
INSTRUCTION DECODER & CONTROL UNIT
ROM EMULATOR / GPIO UNIT
PROGRAM ROM
ACCUMULATOR
16-BIT B REGISTER
PROGRAM COUNTER
ROMULATOR
JUMP LOGIC

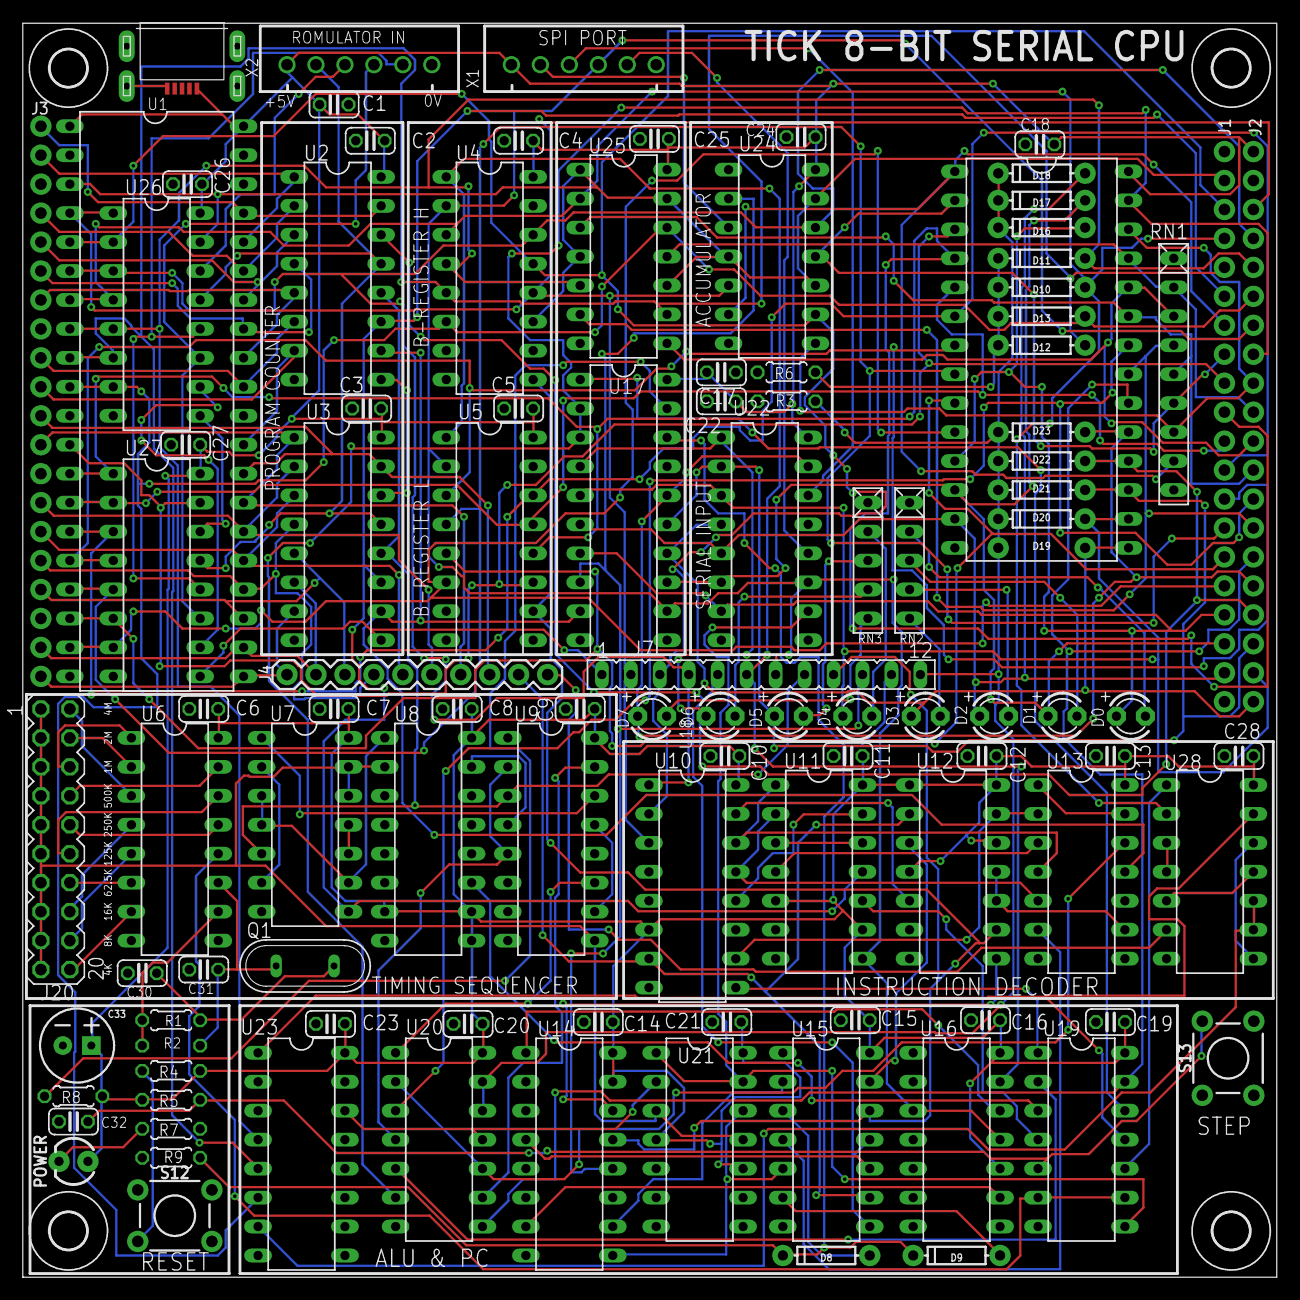
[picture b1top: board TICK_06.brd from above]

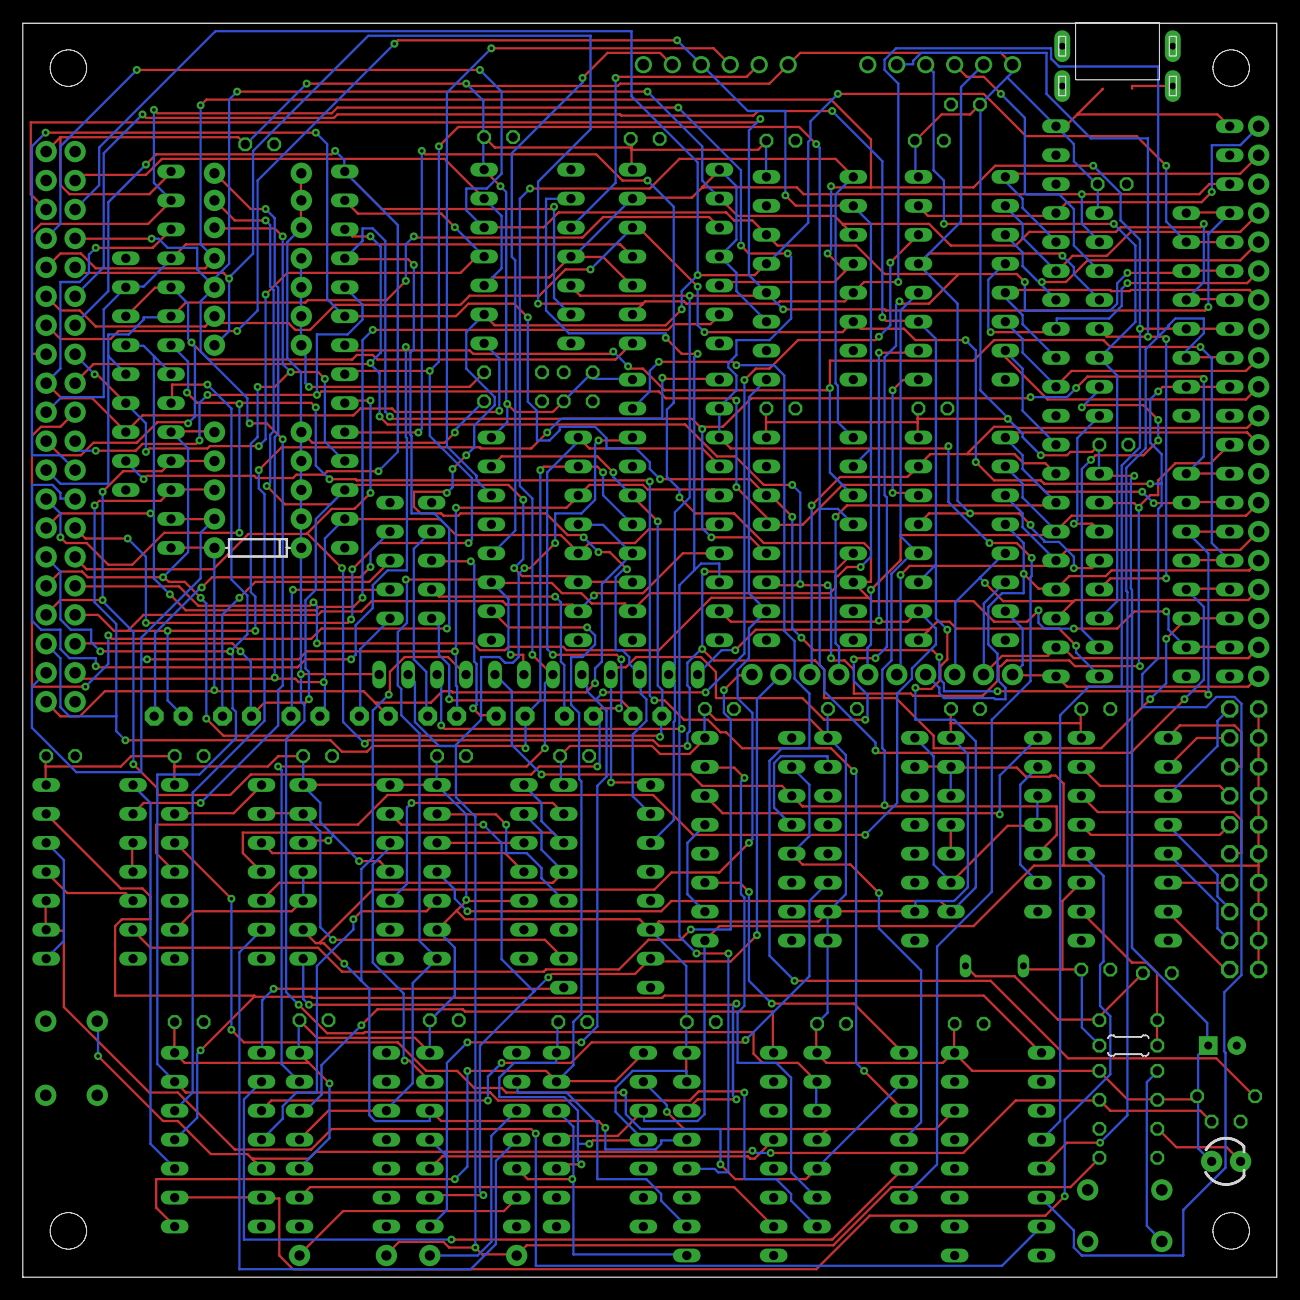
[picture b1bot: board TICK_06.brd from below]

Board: 4 copper layers, 110.0 x 110.0 mm, 111 parts (2 on the bottom side), 145 nets.

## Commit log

2024-09-01 Add files via upload
    Pi Pico/Arduino code to read the Tick Program Counter
2024-09-02 Add files via upload
    Description of Program Counter Operation

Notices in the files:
parts and their libraries:
SparkFun-DiscreteSemi: Licensing: Creative Commons ShareAlike 4.0 International - https://creativecommons.org/licenses/by-sa/4.0
